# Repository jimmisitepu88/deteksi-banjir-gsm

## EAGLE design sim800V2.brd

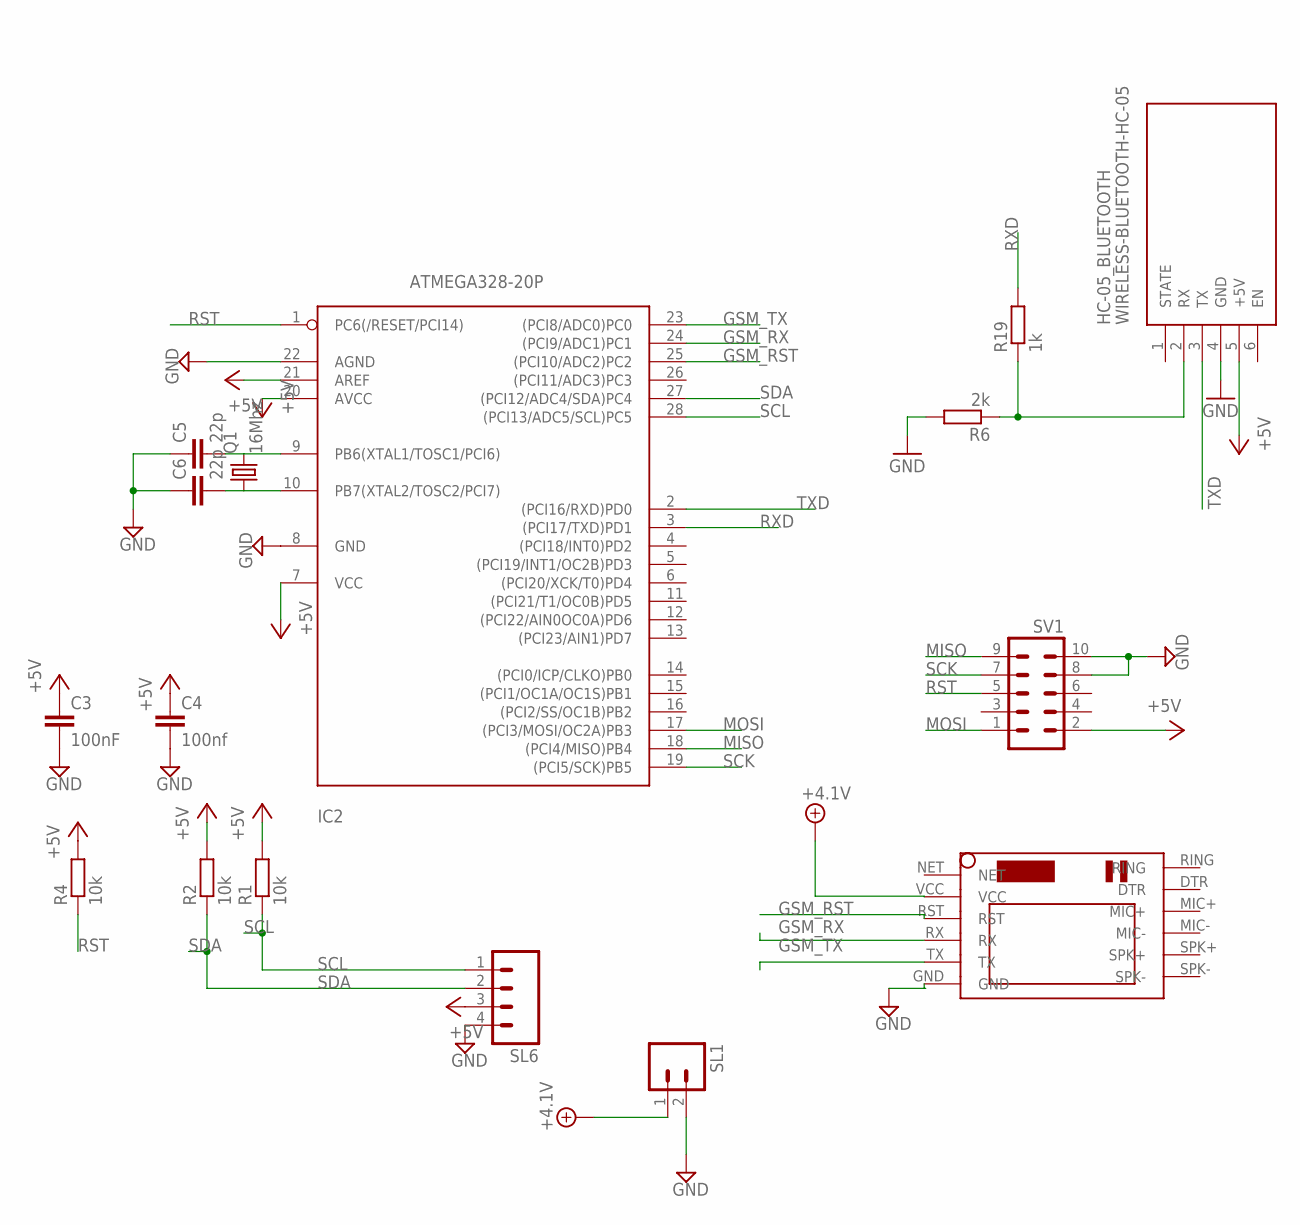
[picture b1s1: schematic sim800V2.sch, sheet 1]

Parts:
C3: 100nF; C050-025X075
C4: 100nf; C050-025X075
C5, C6: 22p; C025-025X050
HC-05_BLUETOOTH: WIRELESS-BLUETOOTH-HC-05
IC2: ATMEGA328-20P; DIL28-3
Q1: 16Mhz; HC49U-V
R1, R2, R4: 10k; 0207/10
R6: 2k; R0805
R19: 1k; R0805
SL1: M02; 02P
SL6: M04; 04P
SV1: ML10
U$1: SIM800LMODULE

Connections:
+4.1V: SL1.1, U$1.VCC; also elsewhere on the board
+5V: C3.1, C4.1, HC-05_BLUETOOTH.5 (+5V), IC2.7 (VCC), IC2.20 (AVCC), IC2.21 (AREF), R1.2, R2.2, R4.2, SL6.3, SV1.2; also elsewhere on the board
GND: C3.2, C4.2, C5.1, C6.1, HC-05_BLUETOOTH.4 (GND), IC2.8 (GND), IC2.22 (AGND), R6.2, SL1.2, SL6.4, SV1.8, SV1.10, U$1.GND; also elsewhere on the board
GSM_RST: IC2.25 ((PCI10/ADC2)PC2), U$1.RST
GSM_RX: IC2.24 ((PCI9/ADC1)PC1), U$1.RX
GSM_TX: IC2.23 ((PCI8/ADC0)PC0), U$1.TX
MISO: IC2.18 ((PCI4/MISO)PB4), SV1.9; also elsewhere on the board
MOSI: IC2.17 ((PCI3/MOSI/OC2A)PB3), SV1.1; also elsewhere on the board
unnamed: C5.2, IC2.9 (PB6(XTAL1/TOSC1/PCI6)), Q1.2
unnamed: C6.2, IC2.10 (PB7(XTAL2/TOSC2/PCI7)), Q1.1
unnamed: HC-05_BLUETOOTH.2 (RX), R6.1, R19.1
RST: IC2.1 (PC6(/RESET/PCI14)), R4.1, SV1.5
RXD: IC2.3 ((PCI17/TXD)PD1), R19.2
SCK: IC2.19 ((PCI5/SCK)PB5), SV1.7; also elsewhere on the board
SCL: IC2.28 ((PCI13/ADC5/SCL)PC5), R1.1, SL6.1
SDA: IC2.27 ((PCI12/ADC4/SDA)PC4), R2.1, SL6.2
TXD: HC-05_BLUETOOTH.3 (TX), IC2.2 ((PCI16/RXD)PD0)

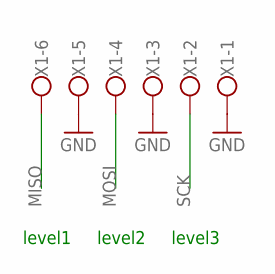
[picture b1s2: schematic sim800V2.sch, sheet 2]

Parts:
X1: W237-136

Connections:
GND: X1.1, X1.3, X1.5; also elsewhere on the board
MISO: X1.6; also elsewhere on the board
MOSI: X1.4; also elsewhere on the board
SCK: X1.2; also elsewhere on the board

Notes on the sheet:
level1
level2
level3

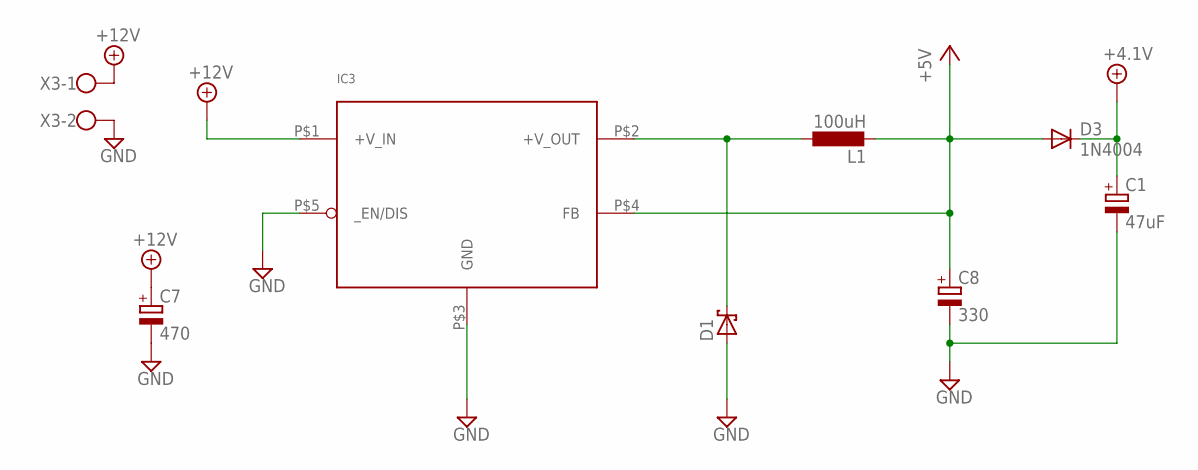
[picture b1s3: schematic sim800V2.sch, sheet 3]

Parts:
C1: 47uF; E2,5-6
C7: 470; E3,5-8
C8: 330; E3,5-8
D1: SCHOTTKY-DIODESMD; SMB
D3: 1N4004; DO41-10
IC3: LM2576-T05D; TO220-5_STAGGERED
L1: 100uH; 6000-XXXX-RC
X3: W237-102

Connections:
+4.1V: C1.+, D3.C; also elsewhere on the board
+5V: C8.+, D3.A, IC3.P$4 (FB), L1.2; also elsewhere on the board
+12V: C7.+, IC3.P$1 (+V_IN), X3.1
GND: C1.-, C7.-, C8.-, D1.A, IC3.P$3 (GND), IC3.P$5 (_EN/DIS), X3.2; also elsewhere on the board
unnamed: D1.C, IC3.P$2 (+V_OUT), L1.1

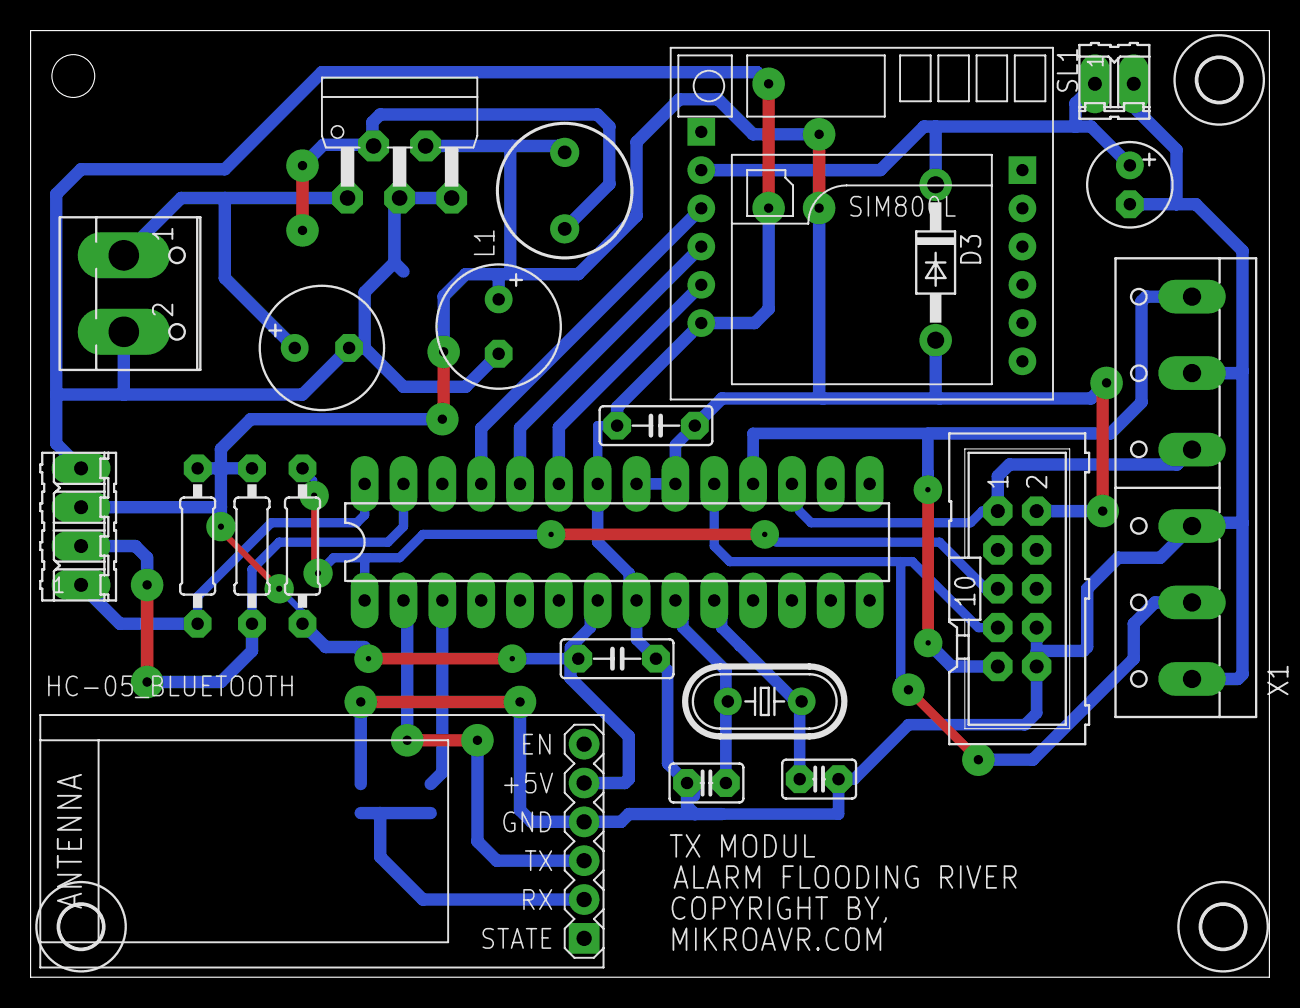
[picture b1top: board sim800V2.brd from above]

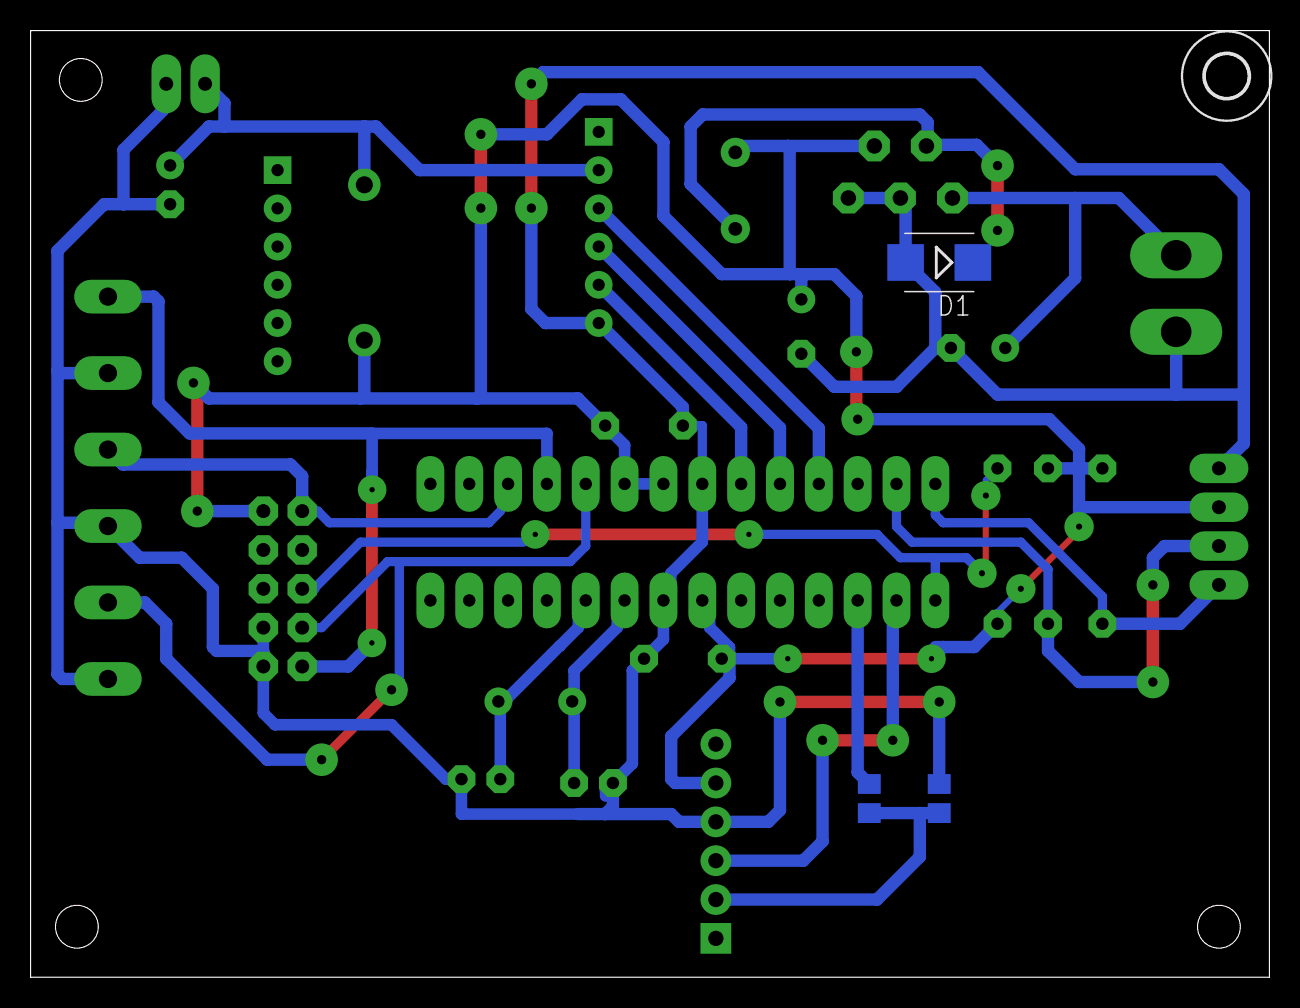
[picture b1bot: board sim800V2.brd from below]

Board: 2 copper layers, 81.0 x 61.9 mm, 29 parts (4 on the bottom side), 19 nets.

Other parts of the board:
U$2, U$3, U$4, U$5: 2,8

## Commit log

2018-11-23 Add files via upload
    circuit for flooding river detectector, when level river change, sms will send to reciver phone number. we use it for preventive action for other people that will be impact
2018-11-23 Add files via upload
    coding for flooding river detection with arduino

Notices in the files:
sim800V2.brd:
COPYRIGHT BY,
parts and their libraries:
diy-modules: Released under the Creative Commons Attribution 4.0 International License: http://creativecommons.org/licenses/by/4.0
